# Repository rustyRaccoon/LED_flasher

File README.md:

# LED_flasher
 Small flashy LEDs to put on your scout scarf

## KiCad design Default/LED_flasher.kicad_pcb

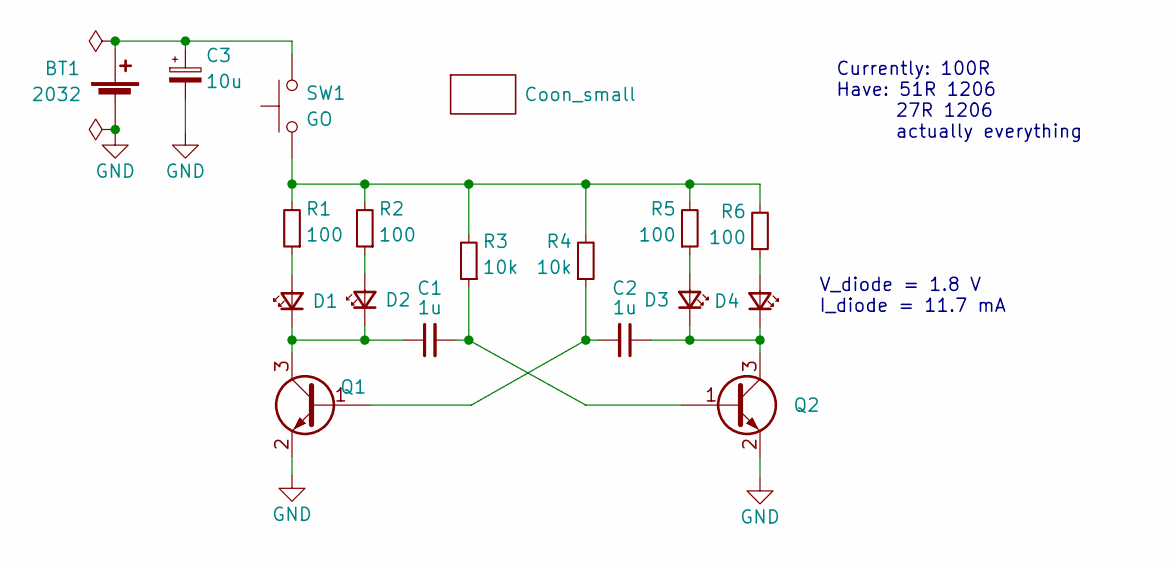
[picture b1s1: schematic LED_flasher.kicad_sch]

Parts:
BT1: 2032; 2032 battery clip
C1, C2: 1u; C_0805_2012Metric_Pad1.18x1.45mm_HandSolder
C3: 10u; CP_EIA-3216-18_Kemet-A
D1, D2, D3, D4: LED_Small; LED_0805_2012Metric_Pad1.15x1.40mm_HandSolder
Q1, Q2: Q_NPN_BEC (BC817K40E6327HTSA1); SOT-23_Handsoldering
R1, R2, R5, R6: 100; R_0805_2012Metric_Pad1.20x1.40mm_HandSolder
R3, R4: 10k; R_0805_2012Metric_Pad1.20x1.40mm_HandSolder
S1: Coon_small; _Racoon_small
SW1: GO; SW_SPST_CK_RS282G05A3

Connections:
GND: BT1.2 (-), C3.2, Q1.2 (E), Q2.2 (E)
unnamed: BT1.1 (+), C3.1, SW1.2
unnamed: C1.1, D1.1 (K), D2.1 (K), Q1.3 (C)
unnamed: C1.2, Q2.1 (B), R3.1
unnamed: C2.1, D3.1 (K), D4.1 (K), Q2.3 (C)
unnamed: C2.2, Q1.1 (B), R4.1
unnamed: D1.2 (A), R1.1
unnamed: D2.2 (A), R2.1
unnamed: D3.2 (A), R5.1
unnamed: D4.2 (A), R6.1
unnamed: R1.2, R2.2, R3.2, R4.2, R5.2, R6.2, SW1.1

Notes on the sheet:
V_diode = 1.8 V I_diode = 11.7 mA
Currently: 100R Have: 51R 1206 27R 1206 actually everything

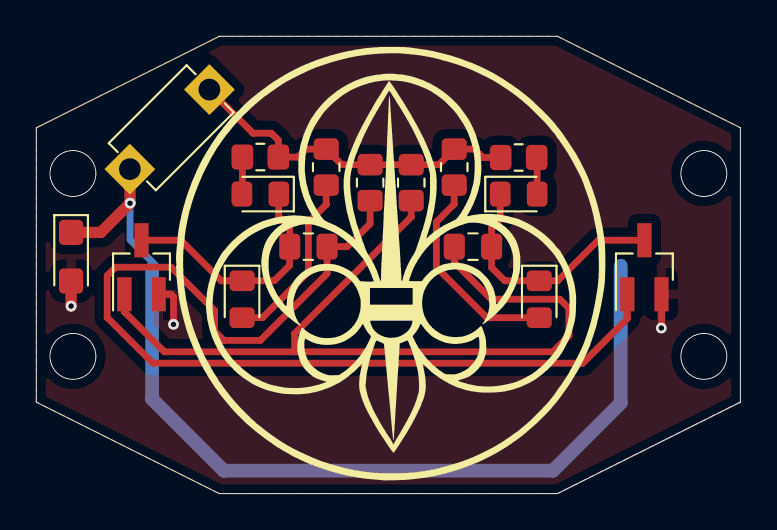
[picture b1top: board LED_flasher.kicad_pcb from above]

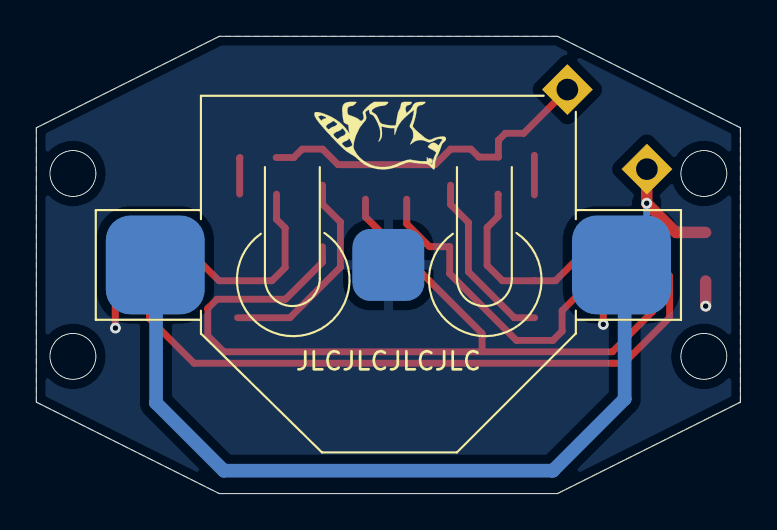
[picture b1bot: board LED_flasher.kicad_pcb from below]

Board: 2 copper layers, 39.1 x 25.4 mm, 18 parts (2 on the bottom side), 11 nets.
